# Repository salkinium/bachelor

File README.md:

Bachelor Thesis Source Code
===========================

This repository contains the entire source code of my bachelor thesis "Temperature Dependency of Bit Error Distributions in Wireless Sensor Networks".

Organisation
------------

This repository is organized as follows:

-	The *box* folder contains the PCB schematics and the CAD drawings and embedded software for the heat box,
- The *experiment_control* folder contains the python software for the experiment server and data logger,
- The *link_analysis* folder contains the python software for analyzing and visualizing experiment results,
- The *motes* folder contains the TinyOS source code for the WSN motes,
- The *position* folder contains CAD drawings of the WSN mote holder,
- The *thesis* folder contains the entire latex source code for my thesis.

[Thesis as PDF](https://github.com/salkinium/bachelor/raw/master/thesis/thesis.pdf).

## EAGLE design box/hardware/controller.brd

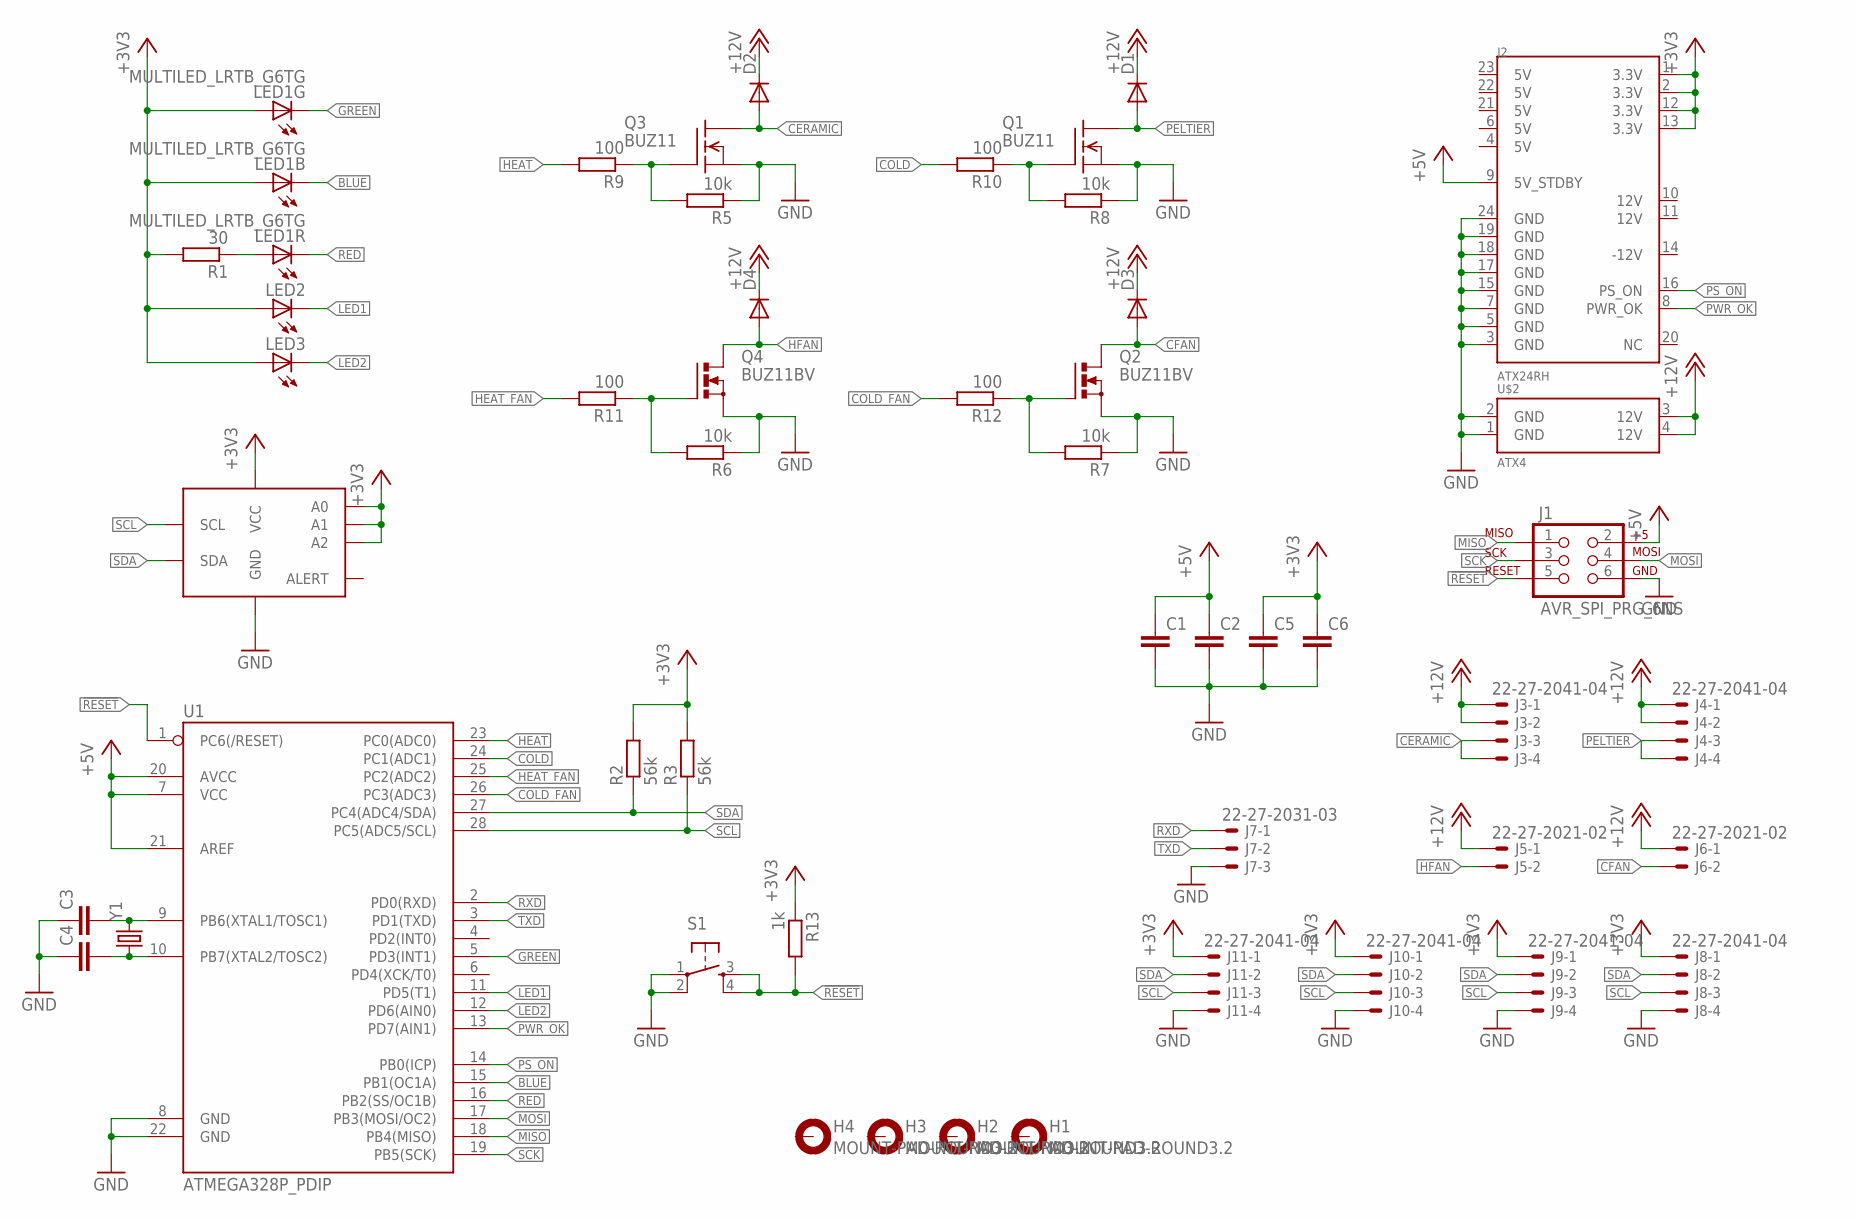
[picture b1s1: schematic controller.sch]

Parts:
C1, C2, C5, C6: C-EUC0603; C0603
C3, C4: C-EUC0603K; C0603K
D1, D2, D3, D4: DIODE-DO201-15; DO201-15
H1, H2, H3, H4: MOUNT-PAD-ROUND3.2; 3,2-PAD
J1: AVR_SPI_PRG_6NS; 2X3-NS
J2: ATX24RH; ATX24_RIGHT_ANGLE
J3, J4, J8, J9, J10, J11: 22-27-2041-04; 6410-04
J5, J6: 22-27-2021-02; 6410-02
J7: 22-27-2031-03; 6410-03
LED1: MULTILED_LRTB_G6TG; P-LCC-6_TOPLED
LED2, LED3: LEDSML1206; SML1206
Q1, Q3: BUZ11; TO220
Q2, Q4: BUZ11BV; TO220BV
R1: 30; R0603
R2, R3: 56k; R0603
R5, R6, R7, R8: 10k; R0603
R9, R10, R11, R12: 100; R0603
R13: 1k; R0603
S1: TAC_SWITCHPTH; TACTILE-PTH
U1: ATMEGA328P_PDIP; DIL28-3
U$1: TMP175; MSOP8
U$2: ATX4
Y1: CRYSTALHC49UV; HC49U-V

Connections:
!RESET: J1.5, R13.2, S1.3, S1.4, U1.1 (PC6(/RESET))
+3V3: C5.1, C6.1, J2.1 (3.3V), J2.2 (3.3V), J2.12 (3.3V), J2.13 (3.3V), J8.1, J9.1, J10.1, J11.1, LED1.A2 (A), LED1.A3 (A), LED2.A, LED3.A, R1.2, R2.2, R3.2, R13.1, U$1.5 (A2), U$1.6 (A1), U$1.7 (A0), U$1.8 (VCC)
+5V: C1.1, C2.1, J1.2, J2.9 (5V_STDBY), U1.7 (VCC), U1.20 (AVCC), U1.21 (AREF)
+12V: D1.C, D2.C, D3.C, D4.C, J3.1, J3.2, J4.1, J4.2, J5.1, J6.1, U$2.3 (12V), U$2.4 (12V)
BLUE: LED1.C3 (C), U1.15 (PB1(OC1A))
CERAMIC: D2.A, J3.3, J3.4, Q3.2 (D)
CFAN: D3.A, J6.2, Q2.D
COLD: R10.2, U1.24 (PC1(ADC1))
COLD_FAN: R12.2, U1.26 (PC3(ADC3))
GND: C1.2, C2.2, C3.1, C4.1, C5.2, C6.2, J1.6, J2.3 (GND), J2.5 (GND), J2.7 (GND), J2.15 (GND), J2.17 (GND), J2.18 (GND), J2.19 (GND), J2.24 (GND), J7.3, J8.4, J9.4, J10.4, J11.4, Q1.3 (S), Q2.S, Q3.3 (S), Q4.S, R5.1, R6.1, R7.1, R8.1, S1.1, S1.2, U1.8 (GND), U1.22 (GND), U$1.4 (GND), U$2.1 (GND), U$2.2 (GND)
GREEN: LED1.C2 (C), U1.5 (PD3(INT1))
HEAT: R9.2, U1.23 (PC0(ADC0))
HEAT_FAN: R11.2, U1.25 (PC2(ADC2))
HFAN: D4.A, J5.2, Q4.D
LED1: LED2.C, U1.11 (PD5(T1))
LED2: LED3.C, U1.12 (PD6(AIN0))
MISO: J1.1, U1.18 (PB4(MISO))
MOSI: J1.4, U1.17 (PB3(MOSI/OC2))
unnamed: C3.2, U1.9 (PB6(XTAL1/TOSC1)), Y1.2
unnamed: C4.2, U1.10 (PB7(XTAL2/TOSC2)), Y1.1
unnamed: LED1.A1 (A), R1.1
unnamed: Q2.G, R7.2, R12.1
unnamed: Q4.G, R6.2, R11.1
unnamed: Q1.1 (G), R8.2, R10.1
unnamed: Q3.1 (G), R5.2, R9.1
PELTIER: D1.A, J4.3, J4.4, Q1.2 (D)
PS_ON: J2.16 (PS_ON), U1.14 (PB0(ICP))
PWR_OK: J2.8 (PWR_OK), U1.13 (PD7(AIN1))
RED: LED1.C1 (C), U1.16 (PB2(SS/OC1B))
RXD: J7.1, U1.2 (PD0(RXD))
SCK: J1.3, U1.19 (PB5(SCK))
SCL: J8.3, J9.3, J10.3, J11.3, R3.1, U1.28 (PC5(ADC5/SCL)), U$1.2 (SCL)
SDA: J8.2, J9.2, J10.2, J11.2, R2.1, U1.27 (PC4(ADC4/SDA)), U$1.1 (SDA)
TXD: J7.2, U1.3 (PD1(TXD))

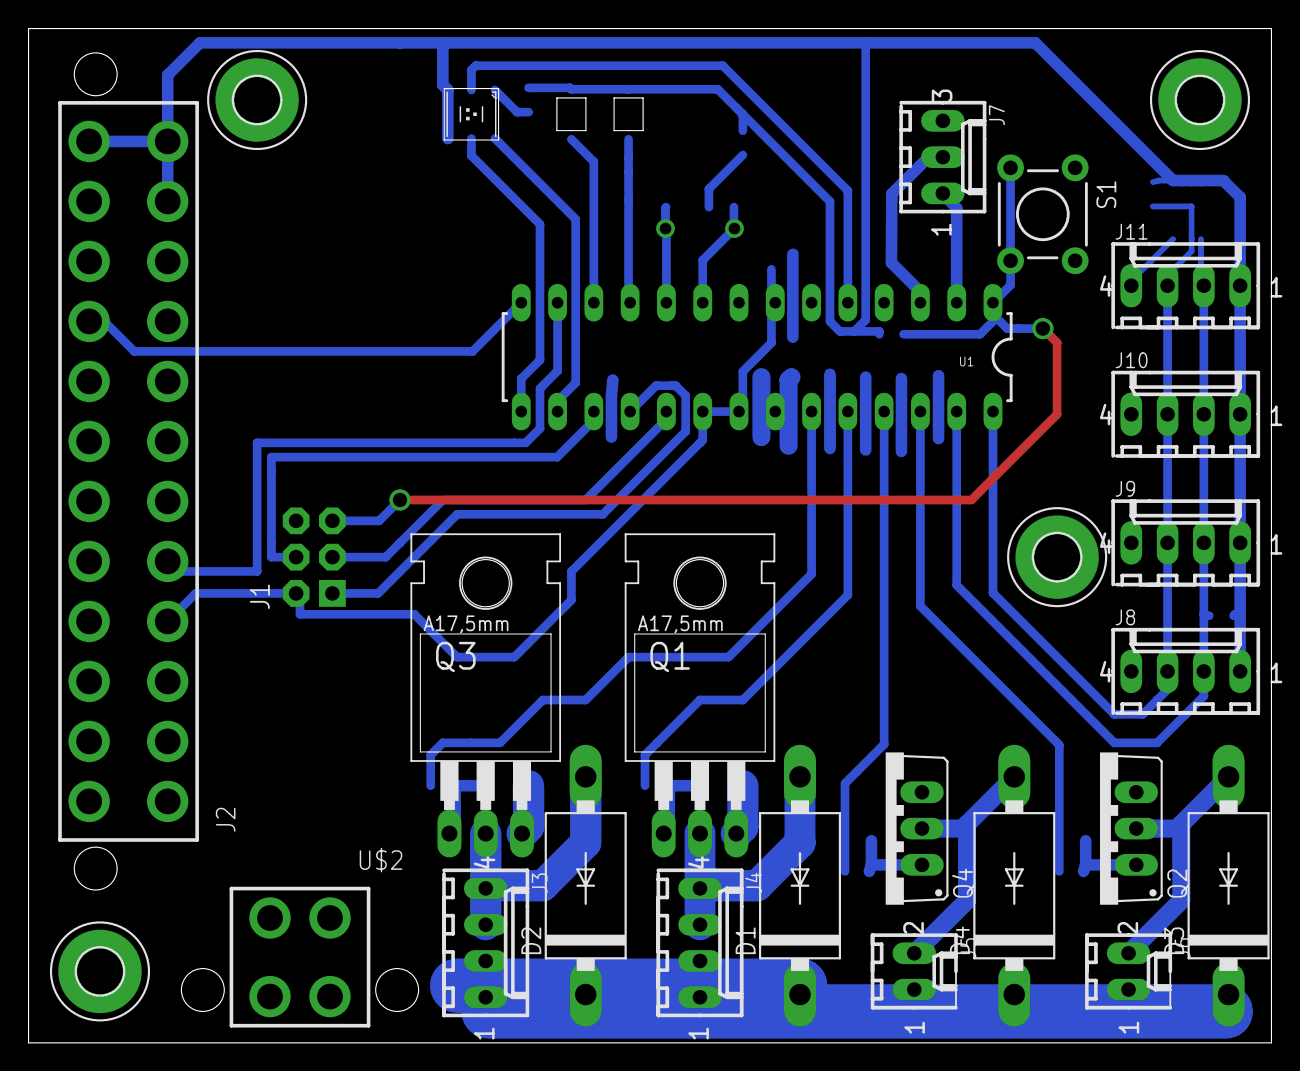
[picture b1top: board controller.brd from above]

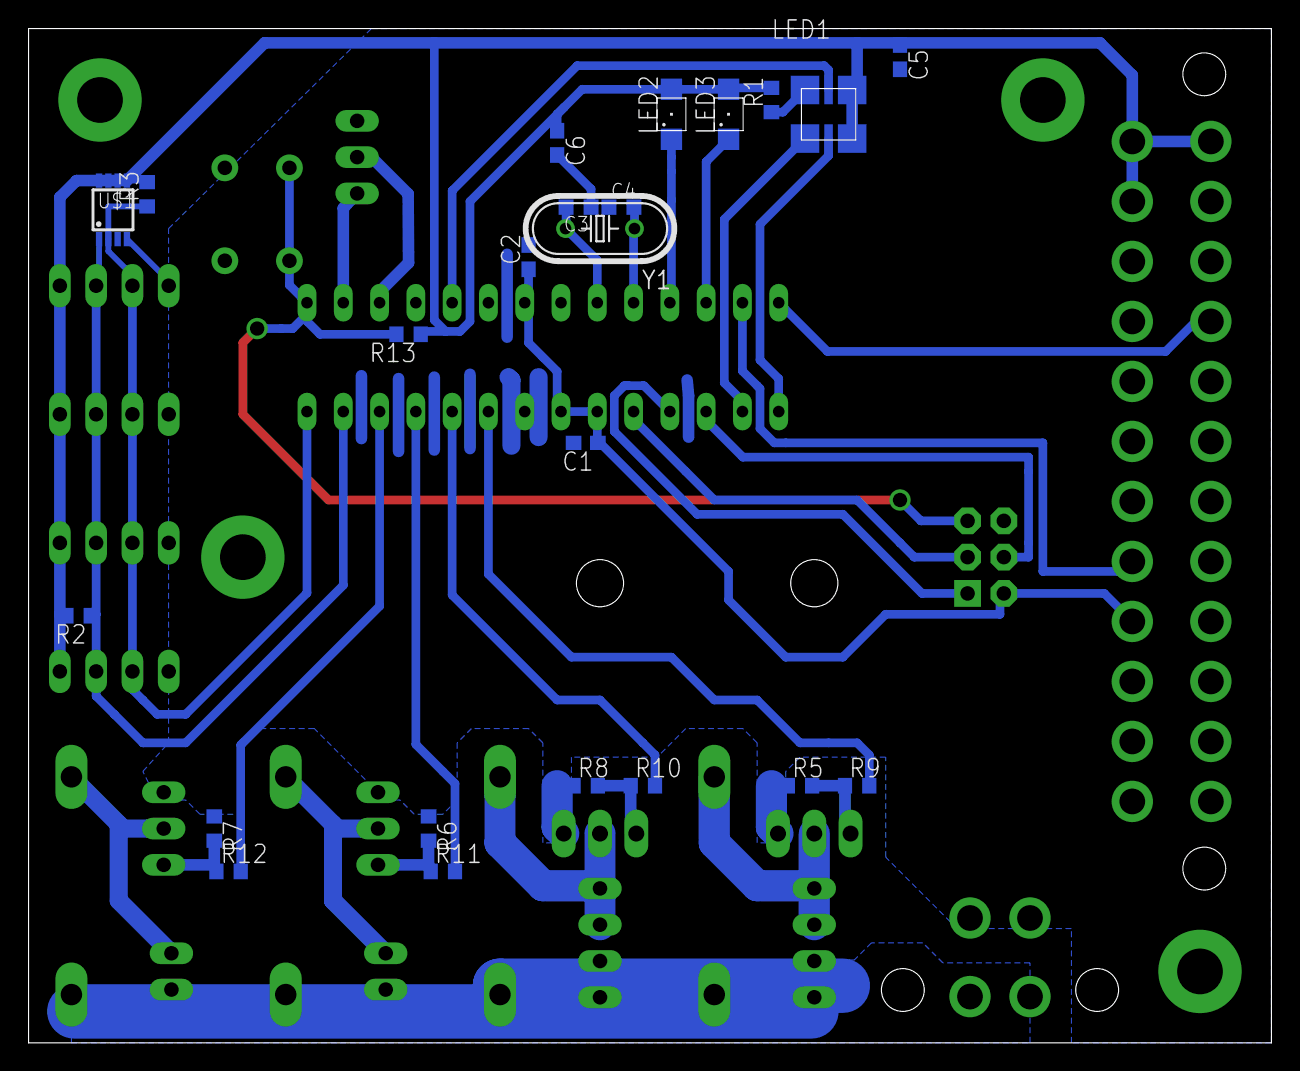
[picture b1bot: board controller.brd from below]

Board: 2 copper layers, 87.0 x 71.0 mm, 49 parts (23 on the bottom side), 34 nets.

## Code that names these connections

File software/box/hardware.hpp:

// coding: utf-8
/* Copyright (c) 2013, Niklas Hauser
* All Rights Reserved.
*
* The file is part of the my thesis and is released under the 3-clause BSD
* license. See the file `LICENSE` for the full license governing this code.
*/
// ----------------------------------------------------------------------------

#ifndef THESIS_HARDWARE
#define THESIS_HARDWARE

#include <xpcc/architecture/platform.hpp>

using namespace xpcc::atmega;

// IO #########################################################################
// ATMEL ATMEGA328P
//                    +-v-+
//     (!RESET) PC6  1|   |28  PC5 (SCL)
//        (RXD) PD0  2|   |27  PC4 (SDA)
//        (TXD) PD1  3|   |26  PC3 (HEAT_FAN)
//              PD2  4|   |25  PC2 (COLD_FAN)
// (GREEN,OC2B) PD3  5|   |24  PC1 (HEAT)
//              PD4  6|   |23  PC0 (COLD)
//              VCC  7|   |22  GND
//              GND  8|   |21  AREF
//      (XTAL1) PB6  9|   |20  AVCC
//      (XTAL2) PB7 10|   |19  PB5 (SCK)
//  (LED2,OC0B) PD5 11|   |18  PB4 (MISO)
//  (LED1,OC0A) PD6 12|   |17  PB3 (MOSI)
//     (PWR_OK) PD7 13|   |16  PB2 (RED,OC1B)
//      (PS_ON) PB0 14|   |15  PB1 (BLUE,OC1A)
//                    +---+

// Color
typedef GpioOutputB2 RedLedPin;
typedef GpioOutputD3 GreenLedPin;
typedef GpioOutputB1 BlueLedPin;

// Signal
typedef GpioOutputD6 WhiteLeftLedPin;
typedef GpioOutputD5 WhiteRightLedPin;

// Power
//typedef GpioOpenDrain<GpioB0> PsOn;
typedef GpioOutputB0 PsOn;
typedef GpioInputD7 PwrOk;

// Control
typedef GpioOutputC1 HeaterPin;
typedef GpioOutputC3 HeaterFanPin;
typedef GpioOutputC0 CoolerPin;
typedef GpioOutputC2 CoolerFanPin;

// Leds
#include "leds.hpp"
WhiteLedLeft whiteLedLeft;
WhiteLedRight whiteLedRight;
RedLed redLed;
GreenLed greenLed;
BlueLed blueLed;

xpcc::ui::RgbLed rgbLed(redLed, greenLed, blueLed);

// COMMUNICATION ##############################################################
// Message
struct SensorData
{
	uint8_t tempData0[2];
	uint8_t tempData1[2];
	uint8_t tempData2[2];
}
sensorMessage __attribute__((packed));

// TMP102 and TMP175 drivers
#include <xpcc/driver/temperature/tmp102.hpp>
#include <xpcc/driver/temperature/tmp175.hpp>
typedef I2cMaster Twi;
xpcc::Tmp175<Twi> sensor0(sensorMessage.tempData0, 0b1001111);
xpcc::Tmp102<Twi> sensor1(sensorMessage.tempData1, 0x48);
//xpcc::Tmp102<Twi> sensor2(sensorMessage.tempData2, 0x49);
//xpcc::Tmp102<Twi> sensor3(sensorMessage.tempData3, 0x4A);
//xpcc::Tmp102<Twi> sensor4(sensorMessage.tempData4, 0x4B);

// Serial debug
#include <xpcc/io/iodevice_wrapper.hpp>
typedef Uart0 Uart;
xpcc::IODeviceWrapper<Uart> logger;

#include <xpcc/debug/logger.hpp>
xpcc::log::Logger xpcc::log::debug(logger);
xpcc::log::Logger xpcc::log::info(logger);
xpcc::log::Logger xpcc::log::warning(logger);
xpcc::log::Logger xpcc::log::error(logger);

#undef	XPCC_LOG_LEVEL
#define	XPCC_LOG_LEVEL xpcc::log::DEBUG


// TASKS ######################################################################
#include "tasks/task_software_pwm.hpp"
task::SoftwarePwm<HeaterPin, 333> heater(whiteLedLeft);
task::SoftwarePwm<HeaterFanPin, 50> heaterFan(whiteLedRight);

#include "tasks/task_temperature.hpp"
task::Temperature temperature;

#endif // THESIS_HARDWARE

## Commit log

2013-09-16 Add xpcc.io as submodule to software.
2013-09-16 Switch xpcc.io to experimental_structure branch.
2013-09-16 Add simple laser cur heater holder.
2013-09-16 Add preliminary test program to read the TMP102. Add instructions for installing/using xpcc.io.
2013-09-16 Add ReadMe and gitignore.
2013-09-18 Add Controller Schematic and Board.
2013-09-18 Hardware: Add fourth hole and different crystal footprint.
2013-09-18 Software: Move hardware instantiation to own file. Add preliminary test Led classes.
2013-09-18 Update xpcc.io. to newest revision.
2013-09-19 Add vector files for lasercut hardware platform.
2013-09-19 Update controller PCB.
2013-09-19 Software: Add all Leds and heartbeat.
2013-09-19 Software: Fix Fast PWM Timer setup for Leds.
2013-09-19 Software: Fix Gpio setup. Add simple command parser to switch things on/off.
2013-09-20 Hardware: Add improved heater holder.
2013-09-23 Software: Add SoftwarePwm Task for controlling Heater and Fan. Update xpcc.io.
2013-09-26 Software: Switch LEDs together with Mosfet.
2013-09-26 Software: Update Led inheritance. Remove heartbeat, as it was annoying.
2013-09-26 Software: Add temperature sensor and evaluation code.
2013-09-27 Software: Replace update() with run(). Some small reordering.
2013-09-27 Software: Add temperature task to wrap all sensor code.
2013-09-27 Software: Update xpcc.io.
2013-09-27 Software: Add TemperatureControl task. Increase Temperature sampling to 250ms. Adapt HSV mapping to 20C (blue) -> 90C (red).
2013-09-27 Software: Update xpcc.io for Led fading time correction.
2013-09-28 Software: Cleanup main loop a little.
2013-09-29 Hardware: Redesign layout of controller PCB.
2013-10-01 Hardware: Add reset push button to PCB.
2013-10-01 Software: Move RGB Led driver to temperature task. Update xpcc.io.
2013-10-01 Hardware: Add Sensor Node holder. Add wind director. Update Baseboard, Fan and heater holder.
2013-10-04 Update xpcc.io.
2013-10-04 Move software/box to software/source.
2013-12-17 Add code to dynamically add temperature sensors. Update xpcc.io.
2013-12-17 Rename all `run()` to `update()`.
2013-12-17 Add IO task to input and output formatting.
2013-12-17 Adapt Gpio for refactoring in xpcc.io.
2013-12-17 Add better way to parse desired temperature input.
2013-12-20 Exchange sensorList for a more efficient one. Nicer sensor outputs. Switch to SoftwareI2c as it is more robust to errors (by just ignoring them).
    Sensor addressing does not work reliably, only one additional sensor is attached.
    This might have something to do with pullups on SCL and SDA, since the cables
    are so long.
    Both Boxes have been tested and both the control loop and communication work.
2014-01-13 Move hardware/ folder into box/ folder.
2014-01-13 Move software/ folder into box/ folder.
2014-01-13 Add tinyos-main repository as submodule.
2014-01-13 Add link analyser python code.
2014-01-15 Add tested python temperature controller.
2014-01-17 Rename TemperatureController -> TemperatureControl.
2014-01-17 Add mig generated python messages.
2014-01-17 Add MoteControl class.
2014-01-19 Fix box firmware. Output of temperature was missing a leading 0 sometimes.
2014-01-19 Add Box class and make it work.
2014-01-19 Update gitignore to ignore box/software/build.
2014-01-19 Add Box class. Add proper python logging. Remove old Logger class.
2014-02-10 Add BoxManager with Script parser. Add proper logging support. Add multiprocessing support.
2014-02-10 Add preliminary experiment script.
2014-02-10 Add temperature input correction interpolation table.
2014-02-20 Working message exchange.
2014-02-20 Add serial test connection.
2014-02-20 Update script.
2014-02-20 Add bi-directional message bursting.
2014-02-20 Add power output of heating element.
2014-02-20 Add better experiment log.
2014-02-21 Add ability to add and execute multiple scripts. Each script now gets its own log.
    Application exits gracefully after all scripts have finished executing.
2014-02-21 Fix the timeout timers.
    Apparently one needs to start them m)
2014-02-22 Wait until mote also reached target temperature. Add mote temperature correction.
2014-02-22 Add first preliminary script.
2014-02-25 Add support for random data. Add scripts for constant and random data exchange at 30C.
2014-02-25 Randomize each message, not just the first one. Last commit also fixes RSSI value and bit error count.
2014-03-02 Objectify link analyser.
2014-03-02 Make experiment output less verbose.
2014-03-03 Add xor plot generator.
2014-03-03 Adapt for adherence to PEP 8.
2014-03-04 Extract evaluation code to Evaluator class.
2014-03-04 Remove the BoxManager god-class code smell, by extracting functionality into their own classes.
    The scripts are now managed and parsed by the ScriptManager, and
    commands are executed using the CommandProcessor design pattern.
    This allows better extensibility and a much cleaner code.
    Now also the correct use of __init__.py. m(
2014-03-05 Rework MessageCommand to consider multiple receipients of messages. Rework output formatting to log full message data. Add sequence numbering to tx and rx messages.
    BaseCommand now adds logger handlers only once.
    More complete error descriptions.
    Rename Evaluator to MessageFormatter.
    Adapt scripts for changes.
2014-03-06 Fix errors with sequence number. Fix scripts.
2014-03-30 Update Link Analysis: - Only one input type supported (StringMessage) - Link class filters rx messages - Fix multiple logger handlers in LinkAnalyzer class. - Add two more experiment parsers.
2014-03-30 Boxes without temperature controller can now be added. Make "wait temperature:" a separate command. Fix message length field in logging. Add experiment harness for 8 nodes.
2014-03-30 Update experiment scripts.
2014-03-30 Add mote position hardware files.
    The mote positioner allows to accurately rotate and distance motes
    against each other. This should allow for better reproducible link
    properties.
2014-04-04 Add rudimentary message visualizer.
2014-04-04 Add experiment harness with visualizer.
2014-04-24 Remove the official tinyos repository submodule.
2014-04-24 Add forked tinyos submodule to add my own changes.
2014-04-24 Add mote programming.
2014-04-24 Add TinyOS Environment. Add motes/Monitoring/build/ folder to gitignore.
2014-04-24 Update tinyos submodule.
2014-04-24 Add WaitCommand for experiment_control.
2014-04-24 Beautify.
2014-04-24 Add temperature test harness and scripts.
2014-04-25 Fix Message AM_TYPE of serial message.
    Never ever use an identifier twice.
    This is the second time I "fixed" this.
2014-04-27 Add more scripts and update harnesses.
2014-04-29 Only heat boxes to 80C.
2014-04-29 Add Reed-Solomon library.
2014-04-29 Add Payload class to take care of message encoding.
2014-04-29 Add coding information to tx message formatter.
2014-05-01 Box: Update interpolation table to remove overshoot.
    The fan will now always stay on, especially during cooldown.
2014-05-01 Add two RS experiment scripts.
2014-05-01 Add box log matplotlib script to create nice plots.
2014-05-01 Add thesis latex document.
    Add preliminary temperature box section with figures.
2014-05-01 Update .gitignore with latex noise.
2014-05-07 Add Bit, Byte and Symbol errors to link.
2014-05-07 Update link analyzer for more and better graphs.
2014-05-07 String message can print itself now.
2014-05-07 Add Baudrate graph plotter.
2014-05-07 Move link parsing from file to its own class.
2014-05-07 Add log splitter for 8mote experiment.
2014-05-07 Add trace-based simulator.
2014-05-07 Update thesis text.
2014-05-07 Add final experiment script.
2014-05-08 Fix header length in simulator.
2014-05-08 Add caching of calculated data.
    This cached calculated raw data as JSON in a txt file,
    so that it can be retrieved without reading the
    entire linkfile again.
2014-05-08 Add figures and tables of bit error classification.
2014-05-09 Add RS decoder to link. Add normalized, chached PRR visualizer. Add processing and time output to LinkFile.
2014-05-09 Small latex update.
2014-05-11 Better command line options for simulator.
2014-05-11 Allow coder to be disabled to save a lot of processing time.
2014-05-11 Add burst error plotting.
2014-05-11 Add burst error generator to simulator.
2014-05-11 Add chapter about bit error pattern simulation.
2014-05-11 Settle for simulator properties, which seem to give the best results for RS testing.
    I do not simulate the header anymore, because the header is not
    evaluated anyway and this only lead to more lost messages.
2014-05-13 Add look at bit errors in the coded message for the PRR plots.
2014-05-17 Update link analyzer to cache all data. Can now create multi-graph figures.
2014-05-17 Add FEC throughput plotter.
2014-05-17 Update thesis.
2014-05-28 Update baudrate_parser to make it more beautiful.
2014-05-28 Update box_parser to make it more beautiful.
2014-05-28 Update FEC plotter to plot multiple graphs.
2014-05-28 Add meaningful error bars to burst error plot.
2014-05-28 Update thesis document. State of submission.
2014-05-28 Add figures. State of submission.
2014-05-28 Add Thesis PDF. State of submission.
2014-07-16 Typo.
2014-07-16 Correct off-by-one error in temperature controller fractional clock generation.
2014-07-16 Added noise reading
2014-09-10 Typos.
2014-09-10 Add 2-clause BSD License.

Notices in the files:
parts and their libraries:
SparkFun-DigitalIC: Licensing: CC v3.0 Share-Alike You are welcome to use this library for commercial purposes.
